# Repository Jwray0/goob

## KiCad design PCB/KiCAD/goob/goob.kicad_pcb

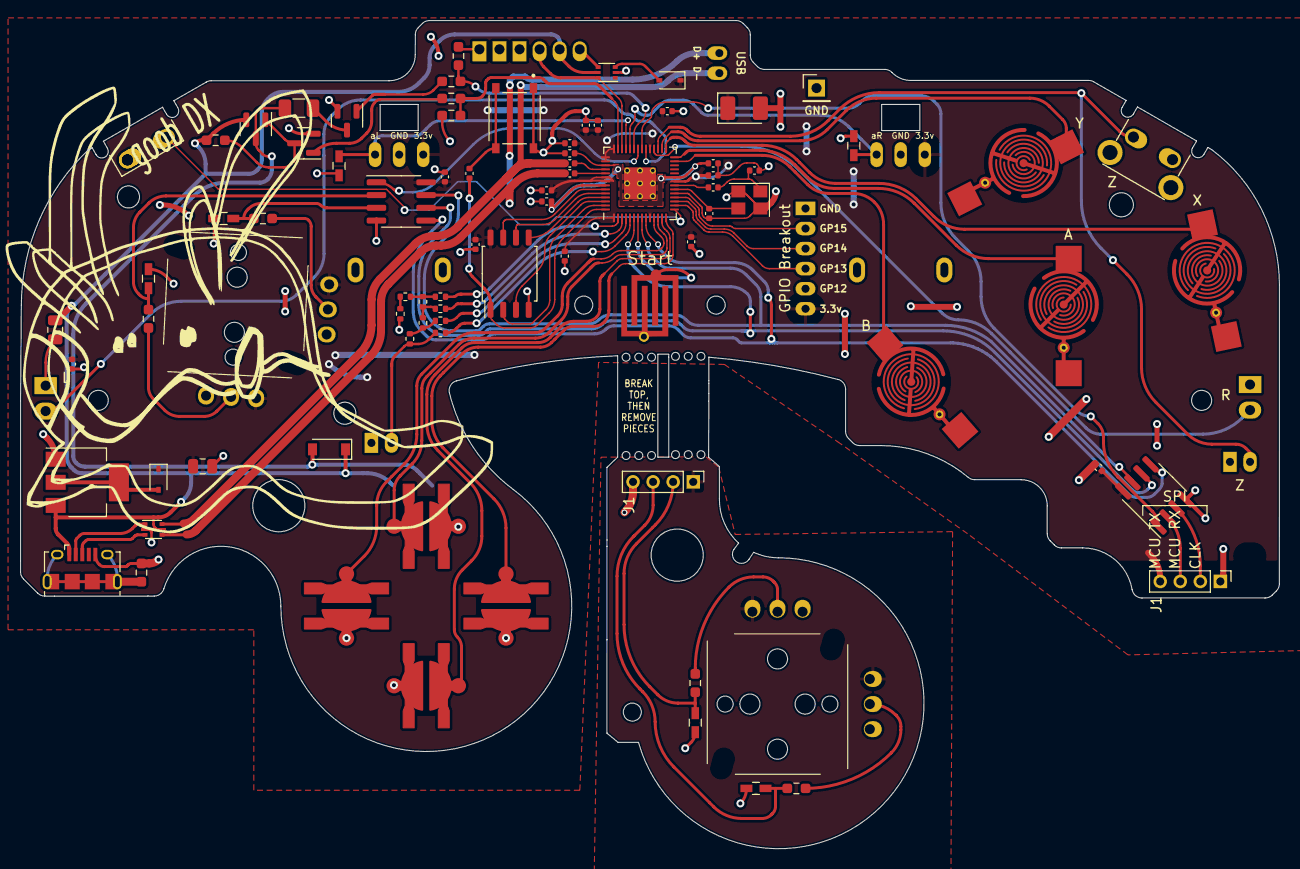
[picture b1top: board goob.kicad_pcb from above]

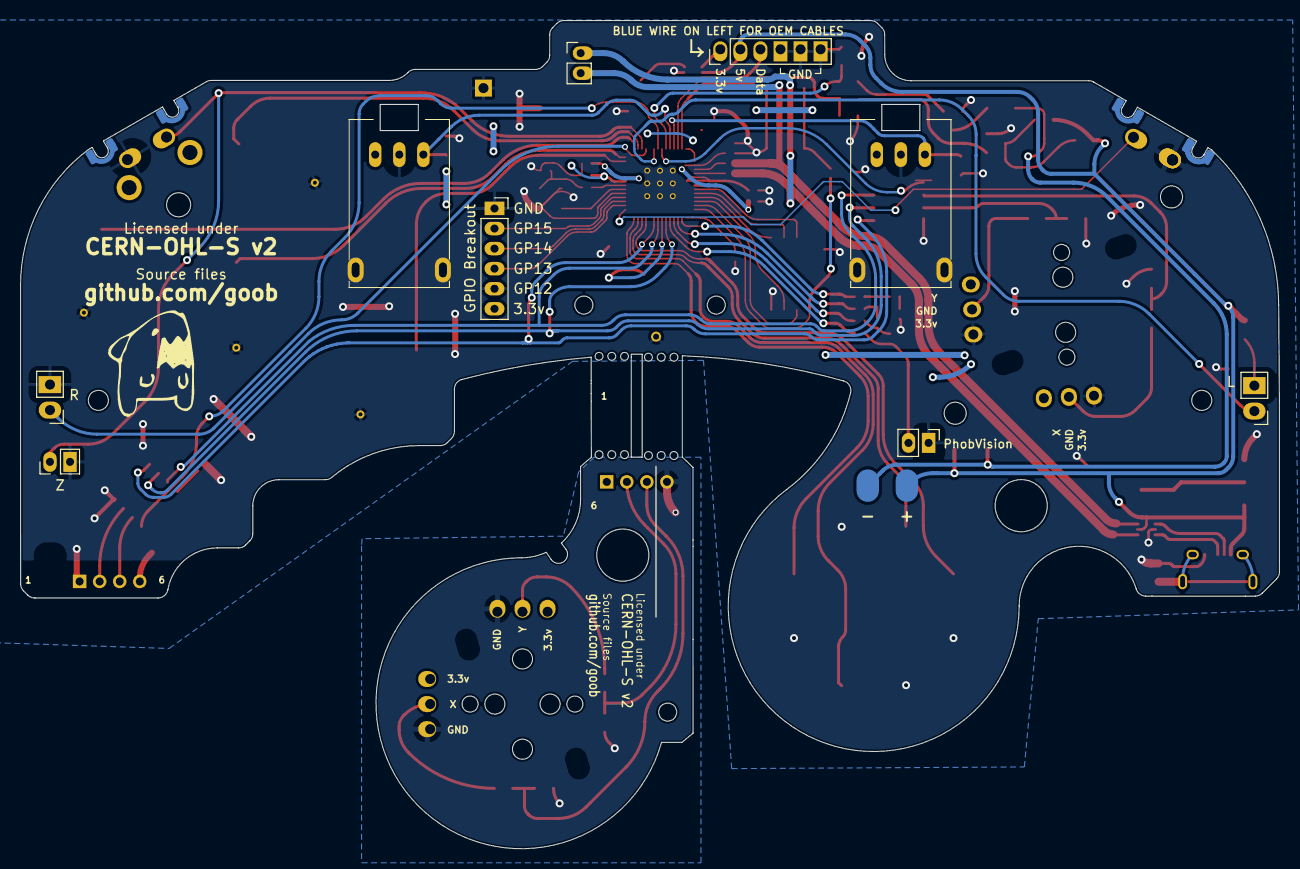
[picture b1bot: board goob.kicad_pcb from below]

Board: 2 copper layers, 125.5 x 82.6 mm, 107 parts (10 on the bottom side), 76 nets.

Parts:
C1: 47u; CP_EIA-3528-12_Kemet-T_Pad1.50x2.35mm_HandSolder
C3, C4, C5, C6, C7, C8: 0.047u; C_0603_HandSoldering
C14, C15: 27p; C_0402_1005Metric
C16, C18: 10u; C_0805_2012Metric
C17, C19, C20, C22, C24, C25, C26, C27, C28, C29, C30, C31, C32: 100n; C_0402_1005Metric
C21, C23: 1u; C_0402_1005Metric
D1, D5: CUS10S30,H3F; D_SOD-323
D2: M7C; D_SOD-123
F1: Fuse; Fuse_1206_3216Metric
H1: 5.2mm; MountingHole_5.2mm
H2: Slot
H3, H4: 2mm; MountingHole_2.0mm
H5, H6: 1.8mm; MountingHole_1.8mm
H7: 2.4mm; MountingHole_2.4mm
H8, H9: 2.2mm; MountingHole_2.2mm
H10: MountingHole; MountingHole_1.8mm
H11: MountingHole; MountingHole_5.2mm
H12, H13: MountingHole; MountingHole_2.0mm
H15, H15#2: MouseBite; breakaway-mousebites-double-v2-large
J1, J1#2: Conn_01x04_Male; PinHeader_1x04_P2.00mm_Vertical
J1#3: Conn_01x06_Female; GCC_Header_Straight_1x06_Pitch2.00mm
J2, J11: Conn_01x02; PinHeader_1x02_P2.00mm_Vertical
J3: Conn_01x02; PinHeader_1x02_P2.00mm_Horizontal
J4: Conn_01x01; PinHeader_1x01_P2.54mm_Vertical
J5: Rumble; rumble_pins
J6: Conn_01x06; PinSocket_1x06_P2.00mm_Vertical
J8: USB_B_Micro; USB_Micro-B_Amphenol_10118194_Horizontal
Q1, Q3: Q_NMOS_GSD; SOT-23
Q2: Q_PMOS_GDS; SOT-23
R1, R2, R7, R8, R9: 180; R_0402_1005Metric
R3, R4, R5, R6: 2k; R_0603_1608Metric_Pad0.98x0.95mm_HandSolder
R10, R19, R24, R25: 316; R_0402_1005Metric
R11, R12: 100R; R_0603_1608Metric_Pad0.98x0.95mm_HandSolder
R13, R14, R15: 10k; R_0603_1608Metric_Pad0.98x0.95mm_HandSolder
R16, R18: 1k; C_0402_1005Metric
R17: 100k; R_0603_1608Metric_Pad0.98x0.95mm_HandSolder
R20, R21: 27; C_0402_1005Metric
RV1, RV2: R_POT_MountingPin; GCC_Slider
S1: BOOTSEL; SW_TS-1187A-B-A-B
SW1: A; ABXY_Contact_Omron_Switch_Circley
SW2: B; ABXY_Contact_Omron_Switch_Circley
SW3: X; ABXY_Contact_Omron_Switch_Circley
SW4: Y; ABXY_Contact_Omron_Switch_Circley
SW5: Start; Start_Contact
SW6: L; Pin_Header_Straight_1x02_Pitch2.54mm
SW7: R; Pin_Header_Straight_1x02_Pitch2.54mm
SW8: Z; Z_Switch_Edge_Omron
SW8L: ZL; Z_Switch_Edge_Omron
SW9: Dleft; Dpad_Contact_TL3315NF_2
SW10: Dup; Dpad_Contact_TL3315NF_2
SW11: Dright; Dpad_Contact_TL3315NF_2
SW12: Ddown; Dpad_Contact_TL3315NF_2
U1, U3: MCP3202; SOIC-8_3.9x4.9mm_P1.27mm
U2, U2#2: 2x DRV5053CAQLPGM Hall Effect Sensors; GCC_Stickbox_2
U6: AMS1117-3.3; SOT-223-3_TabPin2
U7: W25Q128JVS; SOIC-8_5.23x5.23mm_P1.27mm
U8: RP2040; RP2040-QFN-56
U12, U13: USBLC6-2P6; SOT-666
Y1: Crystal_GND24; Crystal_SMD_3225-4Pin_3.2x2.5mm

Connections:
+1V1: C19.1, C20.1, C21.1, U8.23 (DVDD), U8.45 (VREG_VOUT), U8.50 (DVDD)
+3V3: C1.1, C17.1, C18.1, C22.1, C23.1, C24.1, C25.1, C26.1, C27.1, C28.1, C29.1, C30.1, C31.1, C32.1, D1.1 (K), D5.1 (K), J1.4, J6.1, RV1.1 (V+), RV2.1 (V+), U1.8 (VDD/VREF), U2#2.15 (P1XV), U2#2.18 (P1YV), U3.8 (VDD/VREF), U7.8 (VCC), U8.1 (IOVDD), U8.10 (IOVDD), U8.22 (IOVDD), U8.33 (IOVDD), U8.42 (IOVDD), U8.43 (ADC_AVDD), U8.44 (VREG_IN), U8.48 (USB_VDD), U8.49 (IOVDD)
+5V: C16.1, D2.1 (K), J1#3.2, J5.1, J8.1 (VBUS), Q2.2 (S), R13.2, U6.3 (VI), U12.5 (VBUS), U13.5 (VBUS)
/A: SW1.1, U8.28 (GPIO17)
/B: SW2.1, U8.27 (GPIO16)
/Brake: R12.1, R14.2, U8.41 (GPIO29_ADC3)
/CLK: U1.7 (CLK), U3.7 (CLK), U8.8 (GPIO6)
/CS1: U1.1 (~CS/SHDN), U8.36 (GPIO24)
/CS2: U3.1 (~CS/SHDN), U8.35 (GPIO23)
/C_x_filt: C5.1, J1#2.3, R4.1
/C_y_filt: C4.1, J1#2.2, R3.1
/Ddown: SW12.1, U8.13 (GPIO10)
/Din: U1.5 (DIN), U3.5 (DIN), U8.9 (GPIO7)
/Dleft: SW9.1, U8.11 (GPIO8)
/Dout: U1.6 (DOUT), U3.6 (DOUT), U8.6 (GPIO4)
/Dright: SW11.1, U8.14 (GPIO11)
/Dup: SW10.1, U8.12 (GPIO9)
/GCC_3.3V: J1#3.1, U13.4 (I/O2)
/GCC_DATA: J1#3.3, U8.40 (GPIO28_ADC2), U13.6 (I/O1)
/GND_C: C4.2, C5.2, J1#2.4, U2.13 (P1XG), U2.16 (P1YG)
/GPIO13: J6.3, U8.16 (GPIO13)
/GPIO14: J6.4, U8.17 (GPIO14)
/GPIO15: J6.5, U8.18 (GPIO15)
/H1XS: R6.2, U2#2.14 (P1XS)
/H1YS: R5.2, U2#2.17 (P1YS)
/H2XS: R4.2, U2.14 (P1XS)
/H2YS: R3.2, U2.17 (P1YS)
/L: SW6.1, U8.34 (GPIO22)
/Ladder1: R10.2, U8.2 (GPIO0)
/Ladder2: R19.2, U8.3 (GPIO1)
/Ladder3: R24.2, U8.4 (GPIO2)
/Ladder4: R25.2, U8.5 (GPIO3)
/Lanalog: C7.1, RV1.3 (Signal), U8.39 (GPIO27_ADC1)
/LeftZ: SW8L.2, U8.15 (GPIO12)
/QSPI_SCLK: U7.6 (CLK), U8.52 (QSPI_SCLK)
/QSPI_SD0: U7.5 (DI(IO0)), U8.53 (QSPI_SD0)
/QSPI_SD1: U7.2 (DO(IO1)), U8.55 (QSPI_SD1)
/QSPI_SD2: U7.3 (IO2), U8.54 (QSPI_SD2)
/QSPI_SD3: U7.7 (IO3), U8.51 (QSPI_SD3)
/QSPI_SS: R16.1, U7.1 (~CS), U8.56 (QSPI_SS)
/R: SW7.1, U8.32 (GPIO21)
/Ranalog: C3.1, RV2.3 (Signal), U8.38 (GPIO26_ADC0)
/Rumble: R11.1, R15.2, U8.37 (GPIO25)
/Start: SW5.1, U8.7 (GPIO5)
/Stick_x_filt: C8.1, R6.1, U1.2 (CH0)
/Stick_y_filt: C6.1, R5.1, U1.3 (CH1)
/USB_D+: J11.1, R20.1, U12.4 (I/O2)
/USB_D+_Raw: J8.3 (D+), U12.3 (I/O2)
/USB_D-: J11.2, R21.1, U12.6 (I/O1)
/USB_D-_Raw: J8.2 (D-), U12.1 (I/O1)
/V: J2.2, R9.1, R25.1
/X: SW3.1, U8.29 (GPIO18)
/XIN: C14.1, U8.20 (XIN), Y1.3
/XOUT: R18.1, U8.21 (XOUT)
/Y: SW4.1, U8.30 (GPIO19)
/Z: J3.2, SW8.1, U8.31 (GPIO20)
/~USB_BOOT: R16.2, S1.C, S1.D
CX: J1.3, U3.2 (CH0)
CY: J1.2, U3.3 (CH1)
GND: C1.2, C3.2, C6.2, C7.2, C8.2, C14.2, C15.2, C16.2, C17.2, C18.2, C19.2, C20.2, C21.2, C22.2, C23.2, C24.2, C25.2, C26.2, C27.2, C28.2, C29.2, C30.2, C31.2, C32.2, J1.1, J1#3.4, J1#3.5, J1#3.6, J2.1, J3.1, J4.1, J6.2, J6.6, J8.5 (GND), Q1.2 (S), Q3.2 (S), R1.2, R14.1, R15.1, R17.2, RV1.2 (GND), RV2.2 (GND), S1.A, S1.B, SW1.2, SW2.2, SW3.2, SW4.2, SW5.2, SW6.2, SW7.2, SW8.2, SW8L.1, SW9.2, SW10.2, SW11.2, SW12.2, U1.4 (VSS), U2#2.13 (P1XG), U2#2.16 (P1YG), U3.4 (VSS), U6.1 (GND), U7.4 (GND), U8.19 (TESTEN), U8.57 (GND), U12.2 (GND), U13.2 (GND), Y1.2, Y1.4
unnamed: C15.1, R18.2, Y1.1
unnamed: D1.2 (A), U6.2 (VO)
unnamed: D2.2 (A), F1.1, J5.2, Q2.3 (D)
unnamed: D5.2 (A), U13.3 (I/O2)
unnamed: F1.2, Q3.3 (D)
unnamed: J8.6 (Shield), R17.1
unnamed: Q1.1 (G), R12.2
unnamed: Q1.3 (D), Q2.1 (G), R13.1
unnamed: Q3.1 (G), R11.2
unnamed: R1.1, R2.2
unnamed: R2.1, R7.2, R10.1
unnamed: R7.1, R8.2, R19.1
unnamed: R20.2, U8.47 (USB_DP)
unnamed: R21.2, U8.46 (USB_DM)
unnamed: R8.1, R9.2, R24.1
VCC: J1#2.1, U2.15 (P1XV), U2.18 (P1YV)

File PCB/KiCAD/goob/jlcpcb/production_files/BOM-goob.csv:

Comment,Designator,Footprint,LCSC
1k,"R16,R18",C_0402_1005Metric,C11702
USB_B_Micro,J8,USB_Micro-B_Amphenol_10118194_Horizontal,C132563
47u,C1,CP_EIA-3528-12_Kemet-T_Pad1.50x2.35mm_HandSolder,C136751
"CUS10S30,H3F","D1,D5",D_SOD-323,C146335
Q_PMOS_GDS,Q2,SOT-23,C15127
100n,"C17,C19,C20,C22,C24,C25,C26,C27,C28,C29,C30,C31,C32",C_0402_1005Metric,C1525
27p,"C14,C15",C_0402_1005Metric,C1557
10u,"C16,C18",C_0805_2012Metric,C15850
316,"R10,R19,R24,R25",R_0402_1005Metric,C159037
0.047u,"C3,C4,C5,C6,C7,C8",C_0603_HandSoldering,C1622
RP2040,U8,RP2040-QFN-56,C2040
Q_NMOS_GSD,"Q1,Q3",SOT-23,C20917
100R,"R11,R12",R_0603_1608Metric_Pad0.98x0.95mm_HandSolder,C22775
2k,"R3,R4,R5,R6",R_0603_1608Metric_Pad0.98x0.95mm_HandSolder,C22975
27,"R20,R21",C_0402_1005Metric,C25100
100k,R17,R_0603_1608Metric_Pad0.98x0.95mm_HandSolder,C25803
10k,"R13,R14,R15",R_0603_1608Metric_Pad0.98x0.95mm_HandSolder,C25804
USBLC6-2P6,"U12,U13",SOT-666,C2827693
BOOTSEL,S1,SW_TS-1187A-B-A-B,C318884
180,"R1,R2,R7,R8,R9",R_0402_1005Metric,C38941
Crystal_GND24,Y1,Crystal_SMD_3225-4Pin_3.2x2.5mm,C403945
1u,"C21,C23",C_0402_1005Metric,C52923
MCP3202,"U1,U3",SOIC-8_3.9x4.9mm_P1.27mm,C56997
AMS1117-3.3,U6,SOT-223-3_TabPin2,C6186
Fuse,F1,Fuse_1206_3216Metric,C69680
M7C,D2,D_SOD-123,C8598
W25Q128JVS,U7,SOIC-8_5.23x5.23mm_P1.27mm,C97521

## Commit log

2023-07-20 goob
2025-03-06 New PC
2025-04-11 Zl
    Zl

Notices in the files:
PCB/KiCAD/goob/goob.kicad_pcb:
CERN-OHL-S v2
Licensed under
